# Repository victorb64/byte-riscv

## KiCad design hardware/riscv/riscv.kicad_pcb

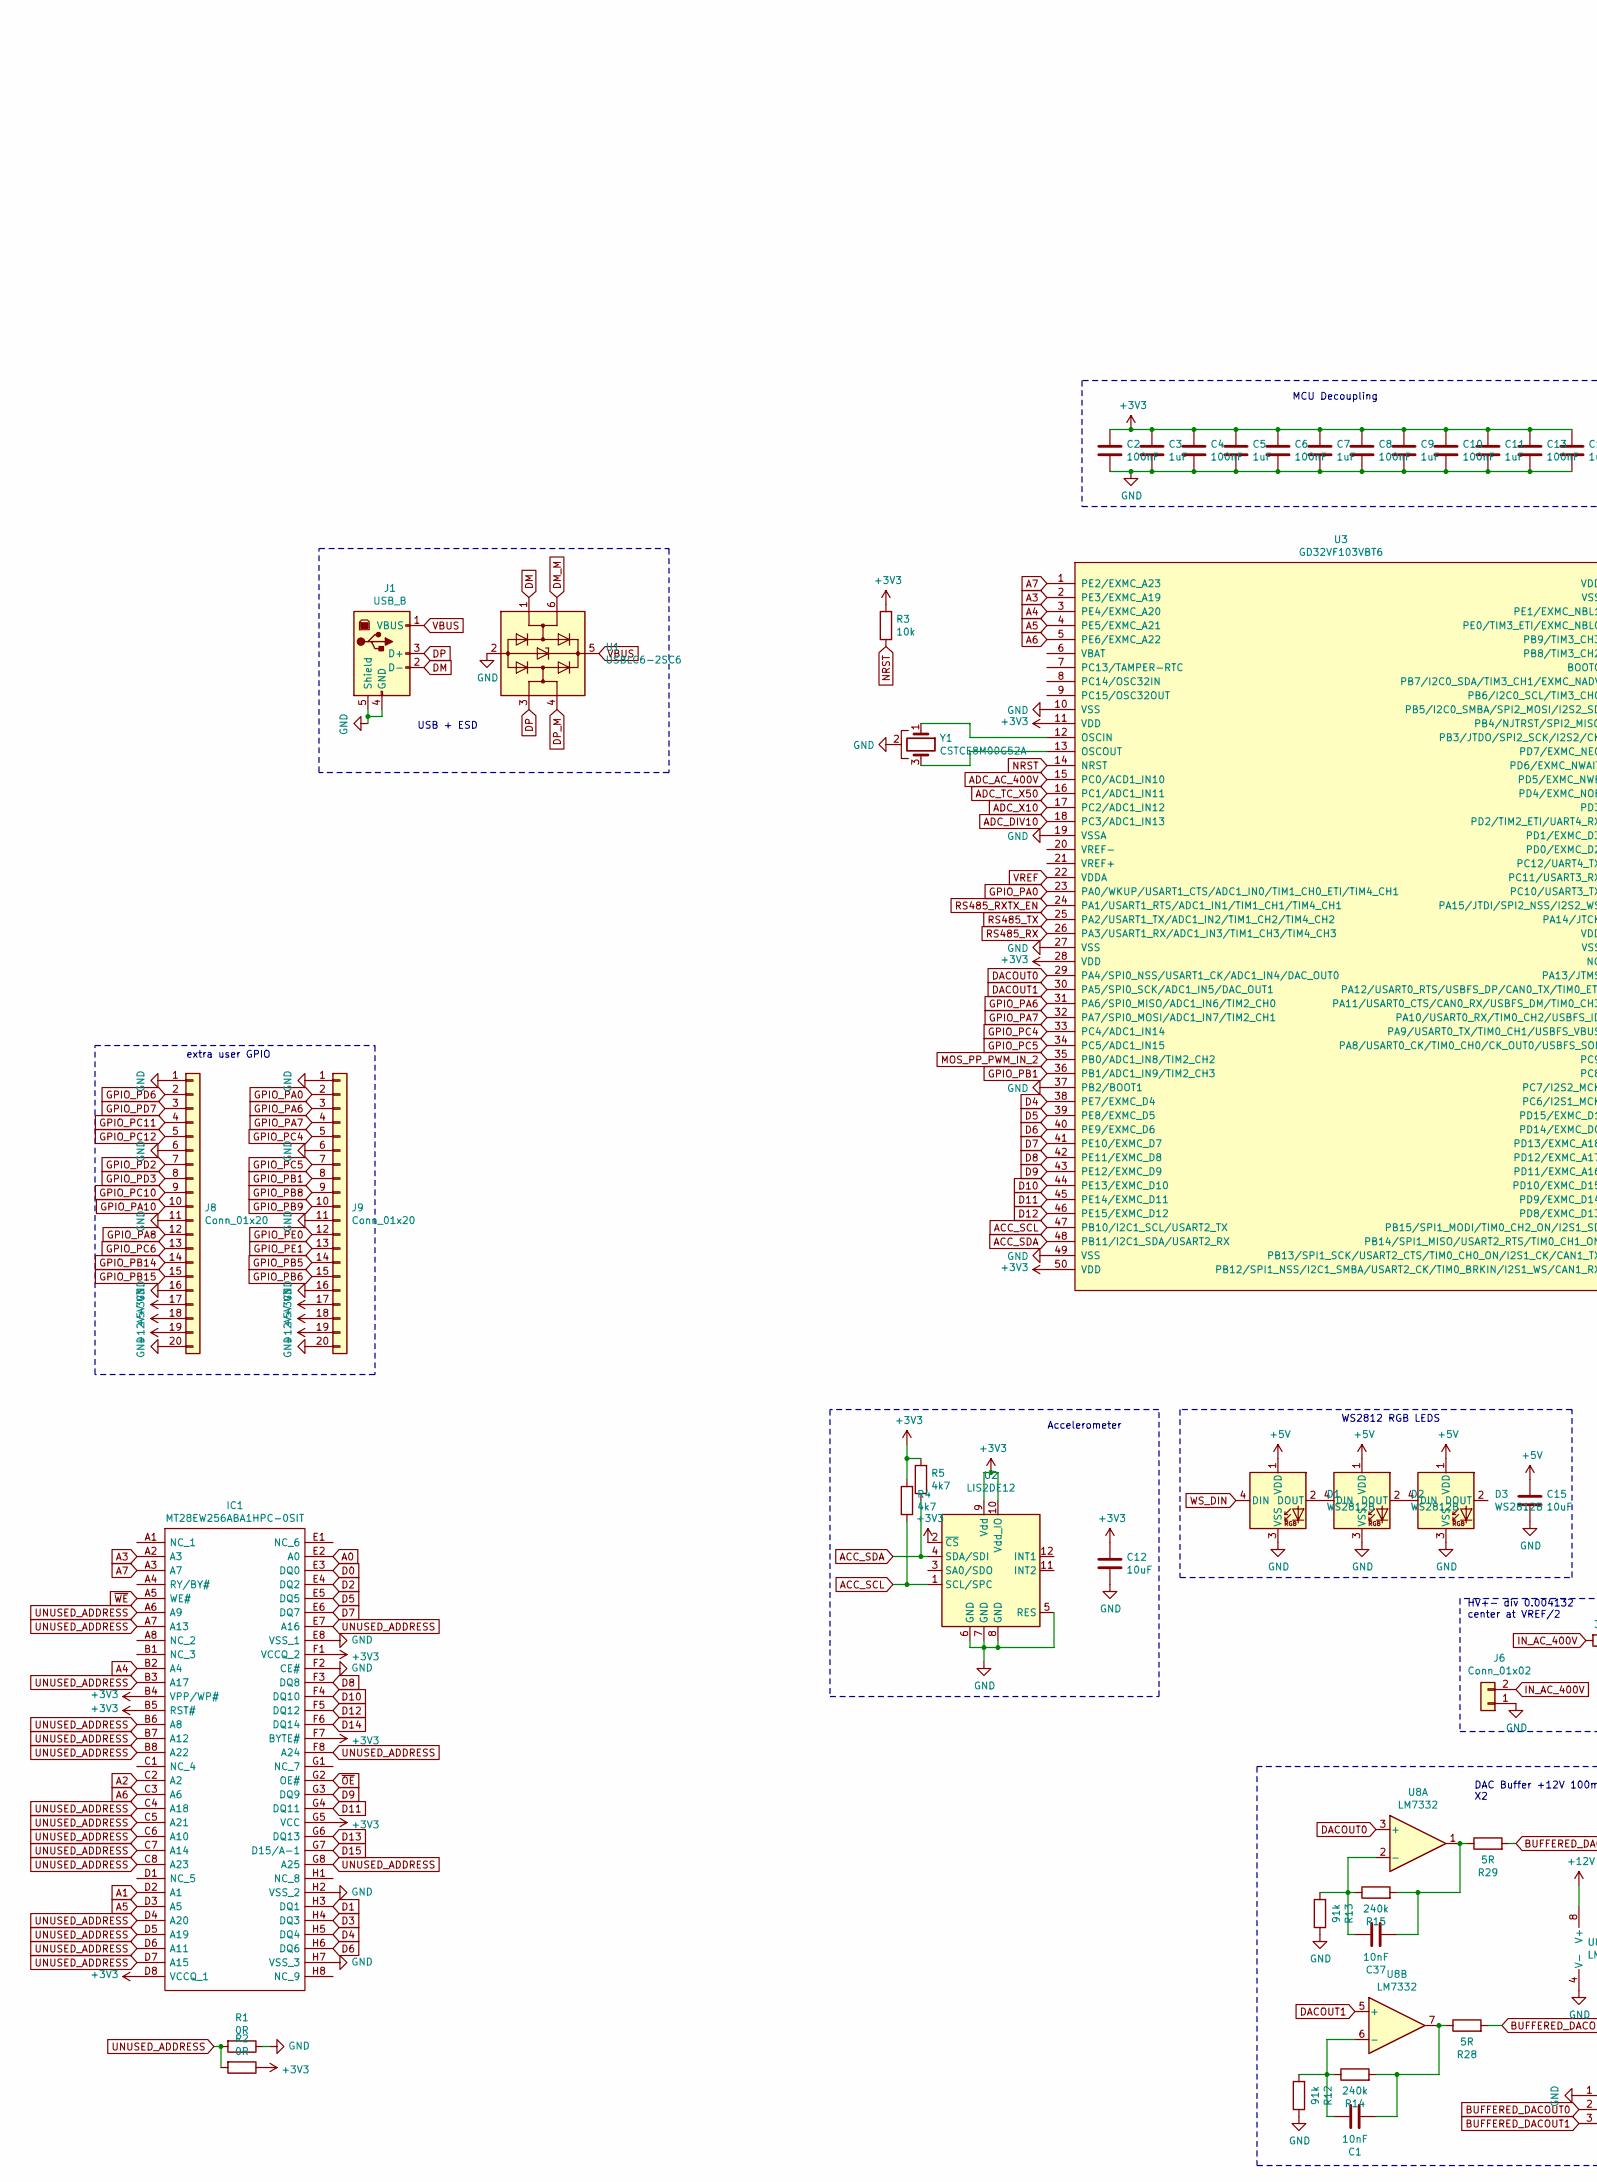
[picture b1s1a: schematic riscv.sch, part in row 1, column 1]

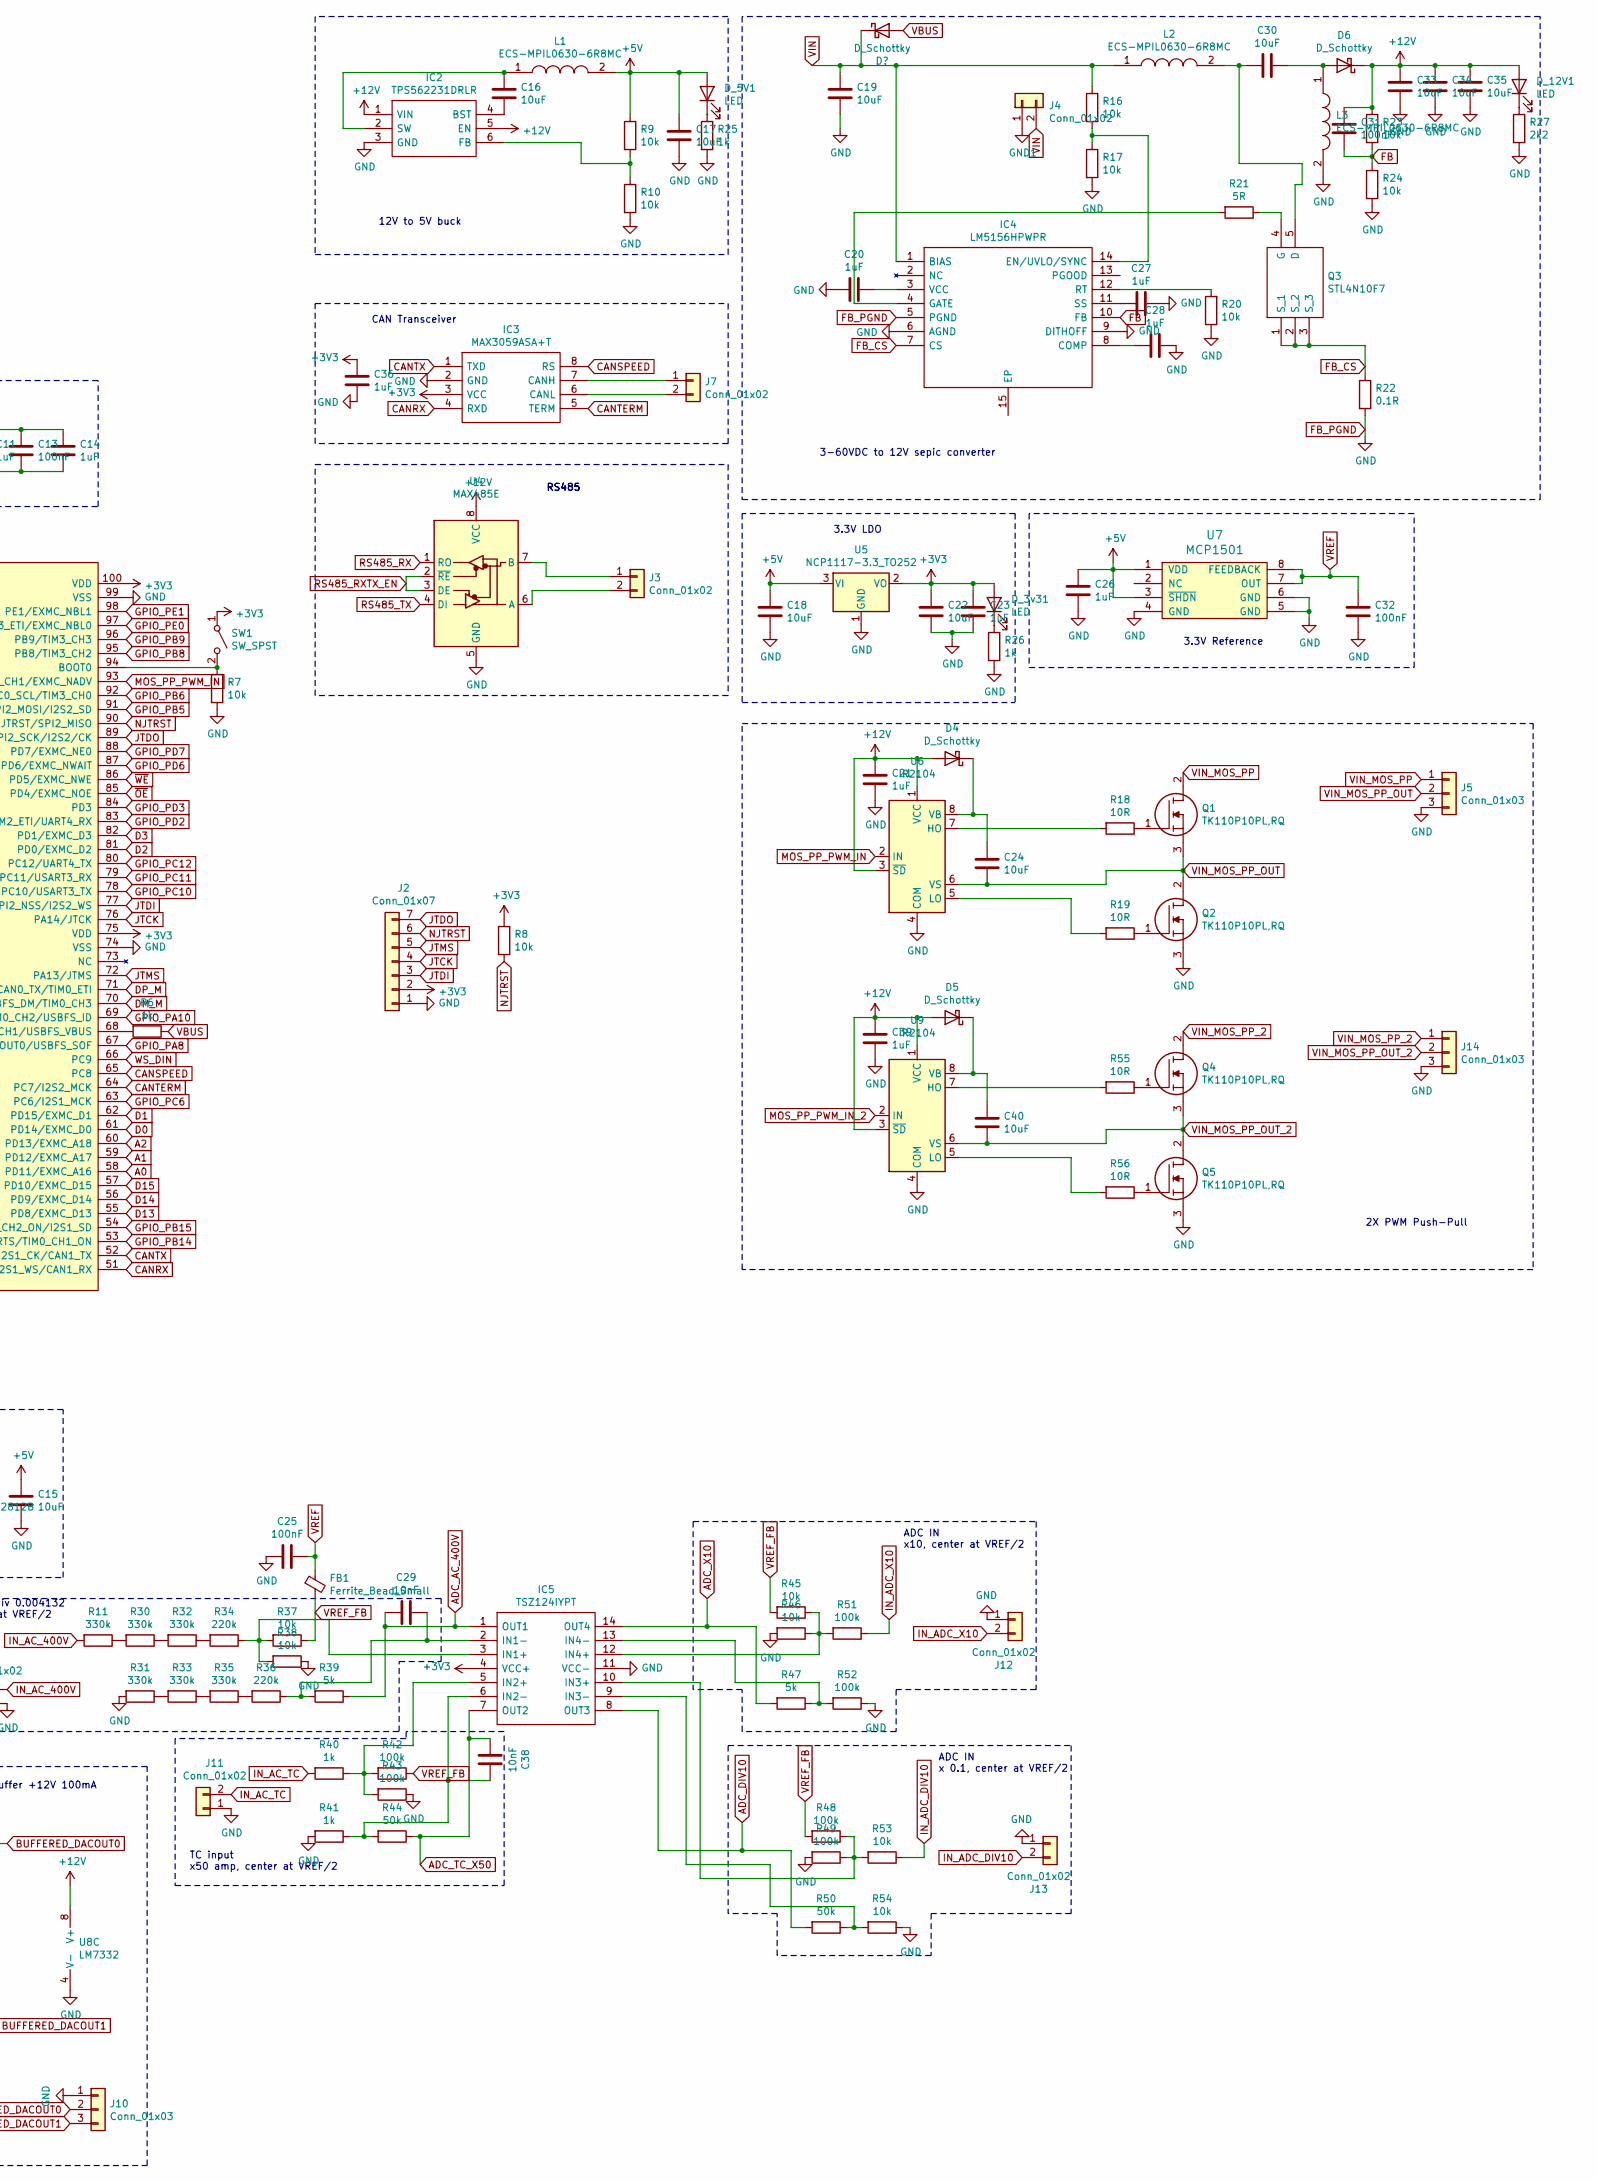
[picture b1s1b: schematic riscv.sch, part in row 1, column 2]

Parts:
C1, C29, C37, C38: 10nF; C_0805
C2, C4, C6, C8, C10, C13, C25, C31, C32: 100nF; C_0805
C3, C5, C7, C9, C11, C14, C21, C23, C26, C27, C28, C36, C39: 1uF; C_0805
C12, C15, C16, C17, C18, C22, C24, C33, C34, C35, C40: 10uF; C_0805
C19, C30: 10uF; C_1210
C20: 1uF; C_1210
D1, D2, D3: WS2812B; LED_Cree-PLCC4_5x5mm_CW
D4, D5, D6: D_Schottky; D_SMA
D_3v31, D_5V1, D_12V1: LED; D_0805
FB1: Ferrite_Bead_Small; R_1206
IC1: MT28EW256ABA1HPC-0SIT; BGA64C100P8X8_1100X1300X140; Manufacturer_Part_Number MT28EW256ABA1HPC-0SIT; Mouser Part Number 340-284307-TRAY
IC2: TPS562231DRLR; SOTFL50P160X60-6N; Manufacturer_Part_Number TPS562231DRLR; Mouser Part Number 595-TPS562231DRLR
IC3: MAX3059ASA+T; SOIC127P600X175-8N; Manufacturer_Part_Number MAX3059ASA+T; Mouser Part Number 700-MAX3059ASAT
IC4: LM5156HPWPR; SOP65P640X120-15N; Manufacturer_Part_Number LM5156HPWPR; Mouser Part Number 595-LM5156HPWPR
IC5: TSZ124IYPT; SOP65P640X120-14N; Manufacturer_Part_Number TSZ124IYPT; Mouser Part Number 511-TSZ124IYPT
J1: USB_B
J2: Conn_01x07; Pin_Header_Straight_1x07_Pitch2.54mm
J3, J4, J6, J7, J11, J12, J13: Conn_01x02; DG235-5.0-02P
J5, J10, J14: Conn_01x03; DG_PB_3
J8, J9: Conn_01x20; Pin_Header_Straight_1x20_Pitch2.54mm
L1, L2, L3: ECS-MPIL0630-6R8MC; INDPM7166X300N; Manufacturer_Part_Number ECS-MPIL0630-6R8MC; Mouser Part Number 520-MPIL0630-6R8MC
Q1, Q2, Q4, Q5: TK110P10PL,RQ; TJ15P04M3RQS; Manufacturer_Part_Number TK110P10PL,RQ; Mouser Part Number 757-TK110P10PLRQ
Q3: STL4N10F7; STL20N6F7; Manufacturer_Part_Number STL4N10F7; Mouser Part Number 511-STL4N10F7
R1, R2: 0R; R_0805
R3, R7, R8, R9, R10, R16, R17, R20, R23, R24, R37, R38, R45, R46, R53, R54: 10k; R_0805
R4, R5: 4k7; R_0805
R6, R25, R26, R40, R41: 1k; R_0805
R11, R30, R31, R32, R33, R35: 330k; R_0805
R12, R13: 91k; R_0805
R14, R15: 240k; R_0805
R18, R19, R55, R56: 10R; R_0805
R21, R28, R29: 5R; R_0805
R22: 0.1R; R_0805
R27: 2k2; R_0805
R34, R36: 220k; R_0805
R39, R47: 5k; R_0805
R42, R43, R48, R49, R51, R52: 100k; R_0805
R44, R50: 50k; R_0805
SW1: SW_SPST; SW_SPST_EVQP2
U1: USBLC6-2SC6; SOT-23-6
U2: LIS2DE12
U3: GD32VF103VBT6; LQFP-100_14x14mm_Pitch0.5mm
U4: MAX485E; SO-8_5.3x6.2mm_Pitch1.27mm
U5: NCP1117-3.3_TO252; TO-252-2
U6, U9: IR2104; SOIC-8_3.9x4.9mm_Pitch1.27mm
U7: MCP1501; SOIC-8_3.9x4.9mm_Pitch1.27mm
U8: LM7332; VSSOP-8_3.0x3.0mm_Pitch0.65mm
Y1: CSTCE8M00G52A; murata CSTCE

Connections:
+3V3: C2.1, C3.1, C4.1, C5.1, C6.1, C7.1, C8.1, C9.1, C10.1, C11.1, C12.1, C13.1, C14.1, C22.1, C23.1, C36.1, D_3v31.2 (A), IC1.B4 (VPP/WP#), IC1.B5 (RST#), IC1.D8 (VCCQ_1), IC1.F1 (VCCQ_2), IC1.F7 (BYTE#), IC1.G5 (VCC), IC3.3 (VCC), IC5.4 (VCC+), J2.2, J8.17, J9.17, R2.1, R3.2, R4.2, R5.2, R8.1, SW1.1 (A), U2.2 (~CS), U2.9 (Vdd), U2.10 (Vdd_IO), U3.11 (VDD), U3.28 (VDD), U3.50 (VDD), U3.75 (VDD), U3.100 (VDD), U5.2 (VO)
+5V: C15.1, C17.1, C18.1, C26.1, D1.1 (VDD), D2.1 (VDD), D3.1 (VDD), D_5V1.2 (A), J8.18, J9.18, L1.2, R9.1, U5.3 (VI), U7.1 (VDD), U7.3 (~SHDN)
+12V: C21.1, C31.2, C33.2, C34.2, C35.2, C39.1, D4.2 (A), D5.2 (A), D6.1 (K), D_12V1.2 (A), IC2.1 (VIN), IC2.5 (EN), J8.19, J9.19, R23.1, U4.8 (VCC), U6.1 (VCC), U6.3 (~SD), U8.8 (V+), U9.1 (VCC), U9.3 (~SD)
A0: IC1.E2 (A0), U3.58 (PD11/EXMC_A16)
A1: IC1.D2 (A1), U3.59 (PD12/EXMC_A17)
A2: IC1.C2 (A2), U3.60 (PD13/EXMC_A18)
A3: IC1.A2 (A3), U3.2 (PE3/EXMC_A19)
A4: IC1.B2 (A4), U3.3 (PE4/EXMC_A20)
A5: IC1.D3 (A5), U3.4 (PE5/EXMC_A21)
A6: IC1.C3 (A6), U3.5 (PE6/EXMC_A22)
A7: IC1.A3 (A7), U3.1 (PE2/EXMC_A23)
ACC_SCL: R4.1, U2.1 (SCL/SPC), U3.47 (PB10/I2C1_SCL/USART2_TX)
ACC_SDA: R5.1, U2.4 (SDA/SDI), U3.48 (PB11/I2C1_SDA/USART2_RX)
ADC_AC_400V: C29.2, IC5.1 (OUT1), R39.1, U3.15 (PC0/ACD1_IN10)
ADC_DIV10: IC5.8 (OUT3), R50.2, U3.18 (PC3/ADC1_IN13)
ADC_TC_X50: C38.2, IC5.7 (OUT2), R44.1, U3.16 (PC1/ADC1_IN11)
ADC_X10: IC5.14 (OUT4), R47.2, U3.17 (PC2/ADC1_IN12)
BUFFERED_DACOUT0: J10.2, R29.2
BUFFERED_DACOUT1: J10.3, R28.2
CANRX: IC3.4 (RXD), U3.51 (PB12/SPI1_NSS/I2C1_SMBA/USART2_CK/TIM0_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)
CANSPEED: IC3.8 (RS), U3.65 (PC8)
CANTERM: IC3.5 (TERM), U3.64 (PC7/I2S2_MCK)
CANTX: IC3.1 (TXD), U3.52 (PB13/SPI1_SCK/USART2_CTS/TIM0_CH0_ON/I2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)
D0: IC1.E3 (DQ0), U3.61 (PD14/EXMC_D0)
D1: IC1.H3 (DQ1), U3.62 (PD15/EXMC_D1)
D2: IC1.E4 (DQ2), U3.81 (PD0/EXMC_D2)
D3: IC1.H4 (DQ3), U3.82 (PD1/EXMC_D3)
D4: IC1.H5 (DQ4), U3.38 (PE7/EXMC_D4)
D5: IC1.E5 (DQ5), U3.39 (PE8/EXMC_D5)
D6: IC1.H6 (DQ6), U3.40 (PE9/EXMC_D6)
D7: IC1.E6 (DQ7), U3.41 (PE10/EXMC_D7)
D8: IC1.F3 (DQ8), U3.42 (PE11/EXMC_D8)
D9: IC1.G3 (DQ9), U3.43 (PE12/EXMC_D9)
D10: IC1.F4 (DQ10), U3.44 (PE13/EXMC_D10)
D11: IC1.G4 (DQ11), U3.45 (PE14/EXMC_D11)
D12: IC1.F5 (DQ12), U3.46 (PE15/EXMC_D12)
D13: IC1.G6 (DQ13), U3.55 (PD8/EXMC_D13)
D14: IC1.F6 (DQ14), U3.56 (PD9/EXMC_D14)
D15: IC1.G7 (D15/A-1), U3.57 (PD10/EXMC_D15)
DACOUT0: U3.29 (PA4/SPI0_NSS/USART1_CK/ADC1_IN4/DAC_OUT0), U8.3 (+)
DACOUT1: U3.30 (PA5/SPI0_SCK/ADC1_IN5/DAC_OUT1), U8.5 (+)
DM: J1.2 (D-), U1.1 (I/O1)
DM_M: U1.6 (I/O1), U3.70 (PA11/USART0_CTS/CAN0_RX/USBFS_DM/TIM0_C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)
DP: J1.3 (D+), U1.3 (I/O2)
DP_M: U1.4 (I/O2), U3.71 (PA12/USART0_RTS/USBFS_DP/CAN0_TX/TIM0_E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)
FB: C31.1, IC4.10 (FB), R23.2, R24.1
FB_CS: IC4.7 (CS), Q3.1 (S_1), Q3.2 (S_2), Q3.3 (S_3), R22.1
FB_PGND: C2.2, C3.2, C4.2, C5.2, C6.2, C7.2, C8.2, C9.2, C10.2, C11.2, C12.2, C13.2, C14.2, C15.2, C17.2, C18.2, C19.2, C20.2, C21.2, C22.2, C23.2, C25.2, C26.2, C27.1, C28.1, C32.2, C33.1, C34.1, C35.1, C36.2, C39.2, D1.3 (VSS), D2.3 (VSS), D3.3 (VSS), IC1.E8 (VSS_1), IC1.F2 (CE#), IC1.H2 (VSS_2), IC1.H7 (VSS_3), IC2.3 (GND), IC3.2 (GND), IC4.5 (PGND), IC4.6 (AGND), IC4.9 (DITHOFF), IC5.11 (VCC-), J1.4 (GND), J1.5 (Shield), J2.1, J5.3, J6.1, J8.1, J8.6, J8.11, J8.16, J8.20, J9.1, J9.6, J9.11, J9.16, J9.20, J10.1, J11.1, J12.1, J13.1, J14.3, L3.2, Q2.3, Q5.3, R1.1, R7.2, R10.2, R12.1, R13.1, R17.2, R20.1, R22.2, R24.2, R25.2, R26.2, R27.2, R31.2, R38.1, R41.2, R43.1, R46.2, R49.2, R52.1, R54.1, U1.2 (GND), U2.5 (RES), U2.6 (GND), U2.7 (GND), U2.8 (GND), U3.10 (VSS), U3.19 (VSSA), U3.27 (VSS), U3.37 (PB2/BOOT1), U3.49 (VSS), U3.74 (VSS), U3.99 (VSS), U4.5 (GND), U5.1 (GND), U6.4 (COM), U7.4 (GND), U7.5 (GND), U7.6 (GND), U8.4 (V-), U9.4 (COM), Y1.2
GND1: J4.1
GPIO_PA0: J9.2, U3.23 (PA0/WKUP/USART1_CTS/ADC1_IN0/TIM1_CH0_E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)
GPIO_PA6: J9.3, U3.31 (PA6/SPI0_MISO/ADC1_IN6/TIM2_CH0)
GPIO_PA7: J9.4, U3.32 (PA7/SPI0_MOSI/ADC1_IN7/TIM2_CH1)
GPIO_PA8: J8.12, U3.67 (PA8/USART0_CK/TIM0_CH0/CK_OUT0/USBFS_SOF)
GPIO_PA10: J8.10, U3.69 (PA10/USART0_RX/TIM0_CH2/USBFS_ID)
GPIO_PB1: J9.8, U3.36 (PB1/ADC1_IN9/TIM2_CH3)
GPIO_PB5: J9.14, U3.91 (PB5/I2C0_SMBA/SPI2_MOSI/I2S2_SD)
GPIO_PB6: J9.15, U3.92 (PB6/I2C0_SCL/TIM3_CH0)
GPIO_PB8: J9.9, U3.95 (PB8/TIM3_CH2)
GPIO_PB9: J9.10, U3.96 (PB9/TIM3_CH3)
GPIO_PB14: J8.14, U3.53 (PB14/SPI1_MISO/USART2_RTS/TIM0_CH1_ON)
GPIO_PB15: J8.15, U3.54 (PB15/SPI1_MODI/TIM0_CH2_ON/I2S1_SD)
GPIO_PC4: J9.5, U3.33 (PC4/ADC1_IN14)
GPIO_PC5: J9.7, U3.34 (PC5/ADC1_IN15)
GPIO_PC6: J8.13, U3.63 (PC6/I2S1_MCK)
GPIO_PC10: J8.9, U3.78 (PC10/USART3_TX)
GPIO_PC11: J8.4, U3.79 (PC11/USART3_RX)
GPIO_PC12: J8.5, U3.80 (PC12/UART4_TX)
GPIO_PD2: J8.7, U3.83 (PD2/TIM2_ETI/UART4_RX)
GPIO_PD3: J8.8, U3.84 (PD3)
GPIO_PD6: J8.2, U3.87 (PD6/EXMC_NWAIT)
GPIO_PD7: J8.3, U3.88 (PD7/EXMC_NE0)
GPIO_PE0: J9.12, U3.97 (PE0/TIM3_ETI/EXMC_NBL0)
GPIO_PE1: J9.13, U3.98 (PE1/EXMC_NBL1)
IN_AC_400V: J6.2, R11.2
IN_AC_TC: J11.2, R40.2
IN_ADC_DIV10: J13.2, R53.1
IN_ADC_X10: J12.2, R51.1
JTCK: J2.4, U3.76 (PA14/JTCK)
JTDI: J2.3, U3.77 (PA15/JTDI/SPI2_NSS/I2S2_WS)
JTDO: J2.7, U3.89 (PB3/JTDO/SPI2_SCK/I2S2/CK)
JTMS: J2.5, U3.72 (PA13/JTMS)
MOS_PP_PWM_IN: U3.93 (PB7/I2C0_SDA/TIM3_CH1/EXMC_NADV), U6.2 (IN)
MOS_PP_PWM_IN_2: U3.35 (PB0/ADC1_IN8/TIM2_CH2), U9.2 (IN)
NJTRST: J2.6, R8.2, U3.90 (PB4/NJTRST/SPI2_MISO)
NRST: R3.1, U3.14 (NRST)
unnamed: C1.1, R12.2, R14.1, U8.6 (-)
unnamed: C1.2, R14.2, R28.1, U8.7
unnamed: C16.1, IC2.2 (SW), L1.1
unnamed: C16.2, IC2.4 (BST)
unnamed: C20.1, IC4.3 (VCC)
unnamed: C24.1, D4.1 (K), U6.8 (VB)
unnamed: C27.2, IC4.11 (SS)
unnamed: C28.2, IC4.8 (COMP)
unnamed: C29.1, IC5.2 (IN1-), R36.1, R39.2
unnamed: C30.1, D6.2 (A), L3.1
unnamed: C30.2, L2.2, Q3.5 (D)
unnamed: C37.1, R13.2, R15.1, U8.2 (-)
unnamed: C37.2, R15.2, R29.1, U8.1
unnamed: C38.1, IC5.6 (IN2-), R41.1, R44.2
unnamed: C40.1, D5.1 (K), U9.8 (VB)
unnamed: D1.2 (DOUT), D2.4 (DIN)
unnamed: D2.2 (DOUT), D3.4 (DIN)
unnamed: D_3v31.1 (K), R26.1
unnamed: D_5V1.1 (K), R25.1
unnamed: D_12V1.1 (K), R27.1
unnamed: IC2.6 (FB), R9.2, R10.1
unnamed: IC3.6 (CANL), J7.2
unnamed: IC3.7 (CANH), J7.1
unnamed: IC4.4 (GATE), R21.2
unnamed: IC4.12 (RT), R20.2
unnamed: IC4.14 (EN/UVLO/SYNC), R16.2, R17.1
unnamed: IC5.3 (IN1+), R34.1, R37.2, R38.2
unnamed: IC5.5 (IN2+), R40.1, R42.2, R43.2
unnamed: IC5.9 (IN3-), R50.1, R54.2
unnamed: IC5.10 (IN3+), R48.1, R49.1, R53.2
unnamed: IC5.12 (IN4+), R45.1, R46.1, R51.2
unnamed: IC5.13 (IN4-), R47.1, R52.2
unnamed: J3.1, U4.7 (B)
unnamed: J3.2, U4.6 (A)
unnamed: Q1.1, R18.1
unnamed: Q2.1, R19.1
unnamed: Q3.4 (G), R21.1
unnamed: Q4.1, R55.1
unnamed: Q5.1, R56.1
unnamed: R6.2, U3.68 (PA9/USART0_TX/TIM0_CH1/USBFS_VBUS)
unnamed: R7.1, SW1.2 (B), U3.94 (BOOT0)
unnamed: R11.1, R30.2
unnamed: R18.2, U6.7 (HO)
unnamed: R19.2, U6.5 (LO)
unnamed: R30.1, R32.2
unnamed: R31.1, R33.2
unnamed: R32.1, R34.2
unnamed: R33.1, R35.2
unnamed: R35.1, R36.2
unnamed: R55.2, U9.7 (HO)
unnamed: R56.2, U9.5 (LO)
unnamed: U3.12 (OSCIN), Y1.1
unnamed: U3.13 (OSCOUT), Y1.3
RS485_RX: U3.26 (PA3/USART1_RX/ADC1_IN3/TIM1_CH3/TIM4_CH3), U4.1 (RO)
RS485_RXTX_EN: U3.24 (PA1/USART1_RTS/ADC1_IN1/TIM1_CH1/TIM4_C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), U4.2 (~RE), U4.3 (DE)
RS485_TX: U3.25 (PA2/USART1_TX/ADC1_IN2/TIM1_CH2/TIM4_CH2), U4.4 (DI)
UNUSED_ADDRESS: IC1.A6 (A9), IC1.A7 (A13), IC1.B3 (A17), IC1.B6 (A8), IC1.B7 (A12), IC1.B8 (A22), IC1.C4 (A18), IC1.C5 (A21), IC1.C6 (A10), IC1.C7 (A14), IC1.C8 (A23), IC1.D4 (A20), IC1.D5 (A19), IC1.D6 (A11), IC1.D7 (A15), IC1.E7 (A16), IC1.F8 (A24), IC1.G8 (A25), R1.2, R2.2
VBUS: J1.1 (VBUS), R6.1, U1.5 (VBUS)
VIN: C19.1, IC4.1 (BIAS), J4.2, L2.1, R16.1
VIN_MOS_PP: J5.1, Q1.2
VIN_MOS_PP_2: J14.1, Q4.2
VIN_MOS_PP_OUT: C24.2, J5.2, Q1.3, Q2.2, U6.6 (VS)
VIN_MOS_PP_OUT_2: C40.2, J14.2, Q4.3, Q5.2, U9.6 (VS)
VREF: C25.1, C32.1, FB1.1, U3.22 (VDDA), U7.7 (OUT), U7.8 (FEEDBACK)
VREF_FB: FB1.2, R37.1, R42.1, R45.2, R48.2
WS_DIN: D1.4 (DIN), U3.66 (PC9)
~OE: IC1.G2 (OE#), U3.85 (PD4/EXMC_NOE)
~WE: IC1.A5 (WE#), U3.86 (PD5/EXMC_NWE)

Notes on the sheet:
MCU Decoupling
3.3V Reference
3.3V LDO
3-60VDC to 12V sepic converter
WS2812 RGB LEDS
Accelerometer
HV+- div 0.004132 center at VREF/2
TC input x50 amp, center at VREF/2
DAC Buffer +12V 100mA X2
ADC IN x10, center at VREF/2
ADC IN x 0.1, center at VREF/2
extra user GPIO
USB + ESD
12V to 5V buck
CAN Transceiver
RS485
2X PWM Push-Pull

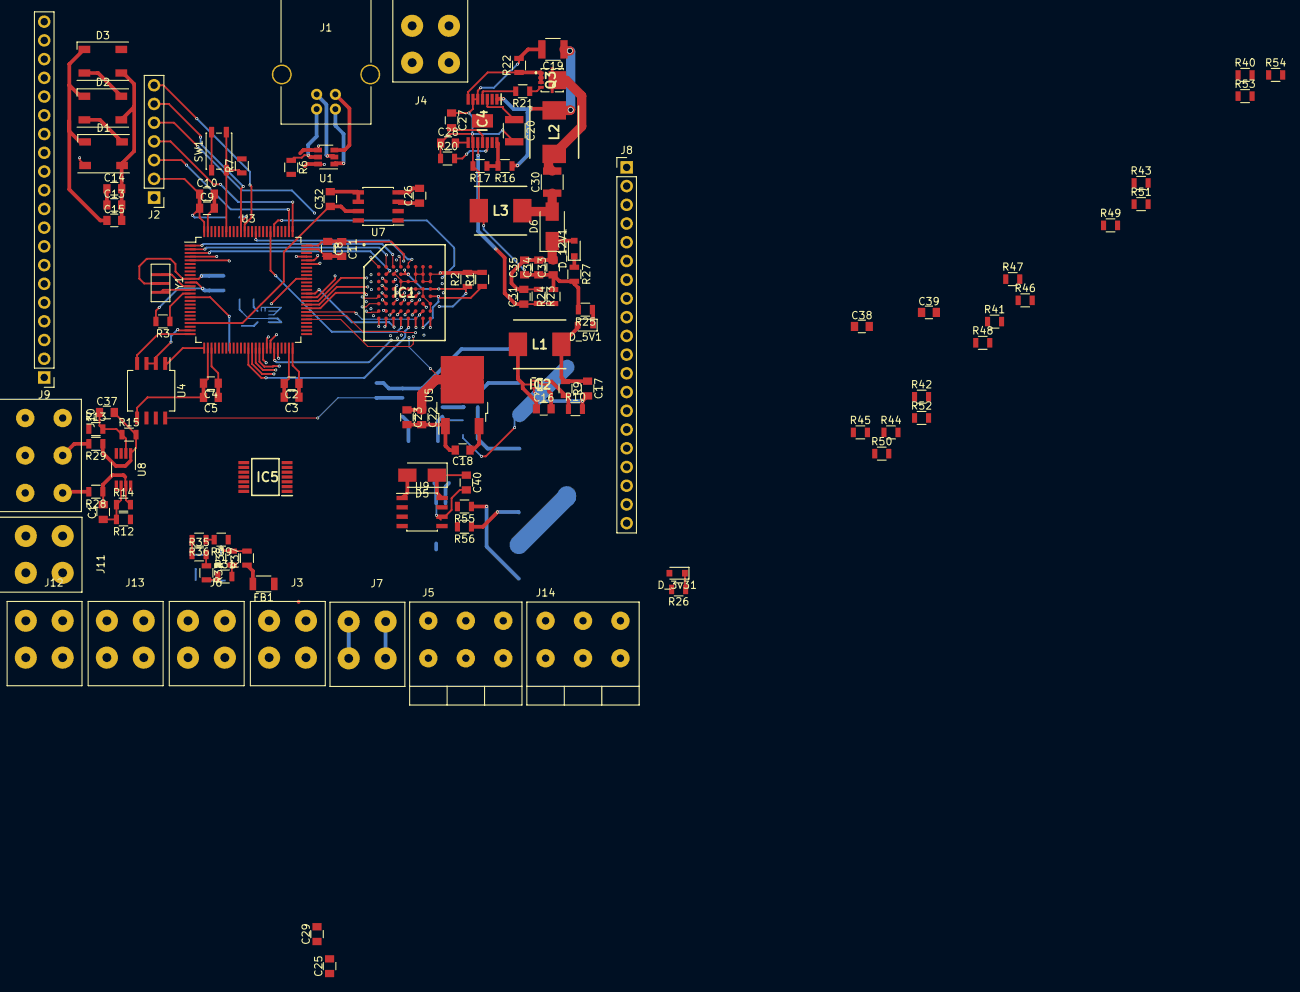
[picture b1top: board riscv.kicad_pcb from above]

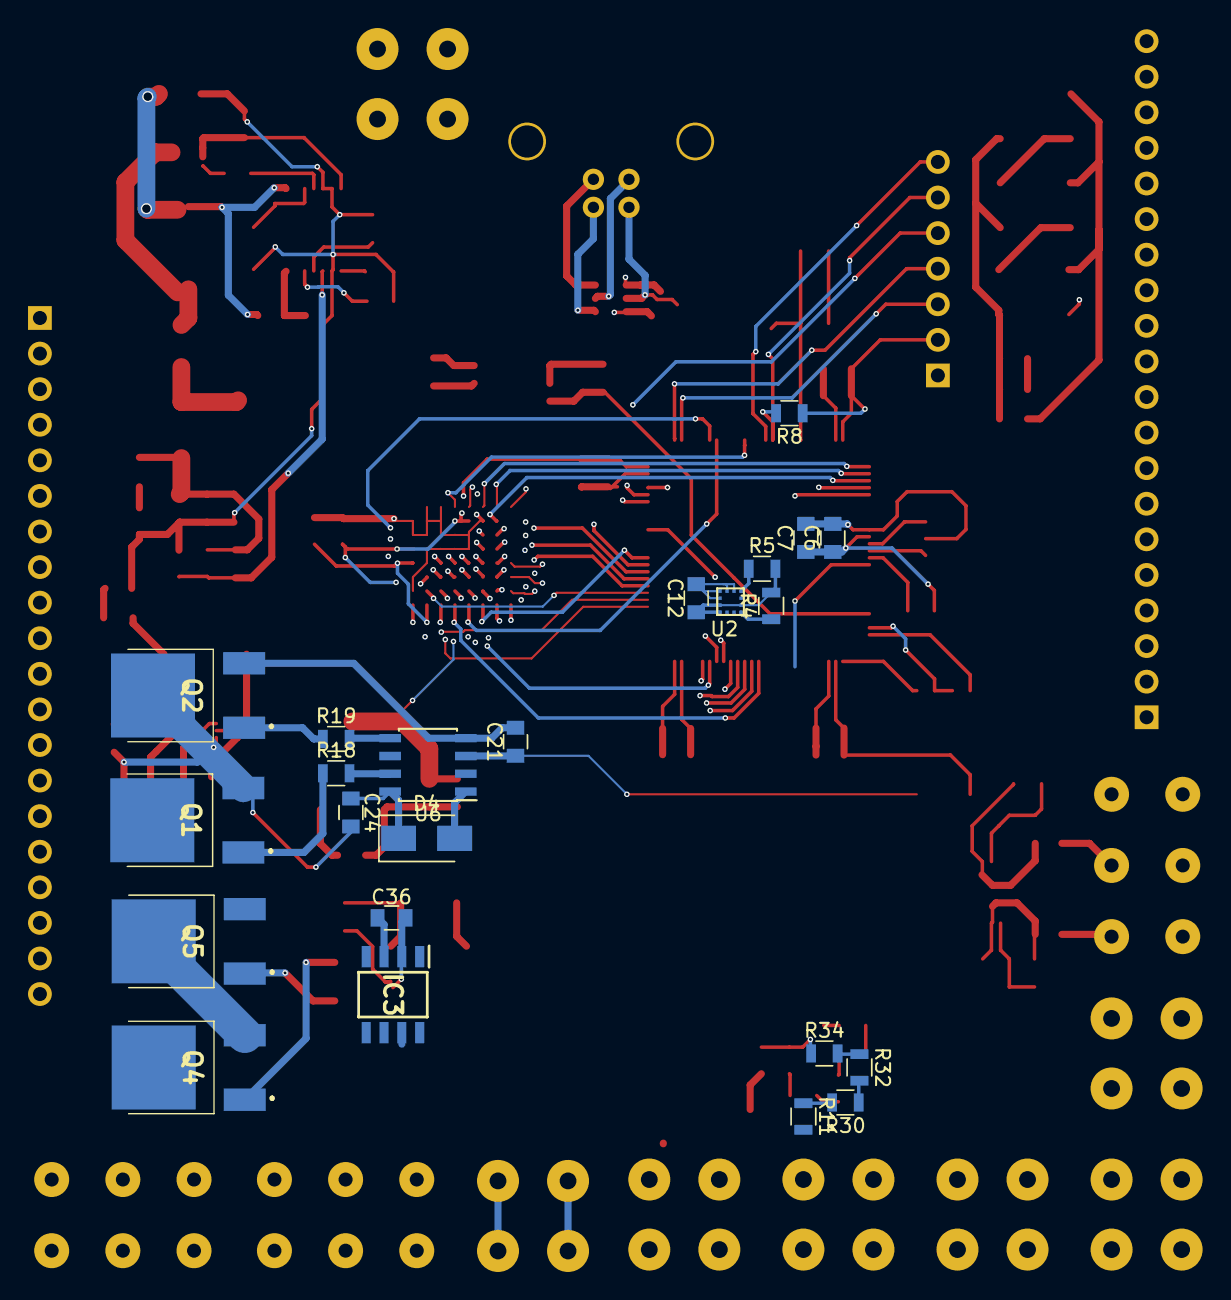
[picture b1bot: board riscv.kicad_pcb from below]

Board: 4 copper layers, 144 parts (23 on the bottom side), 152 nets.

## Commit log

2021-03-06 initial
2021-03-06 sch should be fine now
2021-03-06 rough positioning
